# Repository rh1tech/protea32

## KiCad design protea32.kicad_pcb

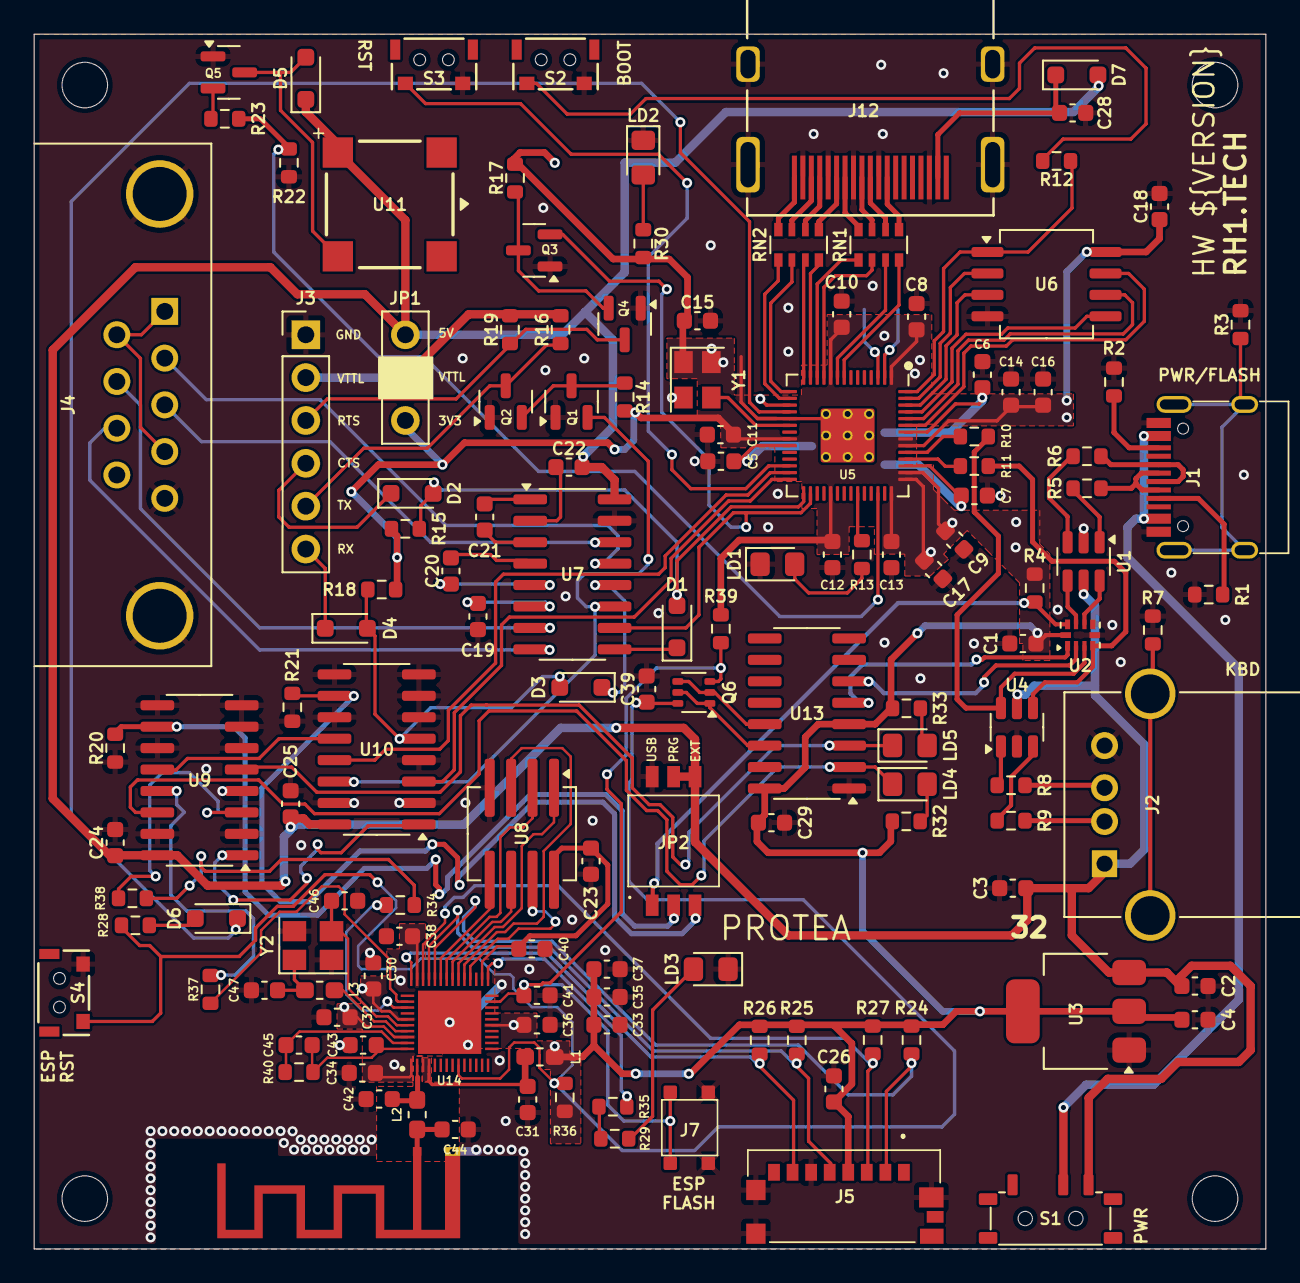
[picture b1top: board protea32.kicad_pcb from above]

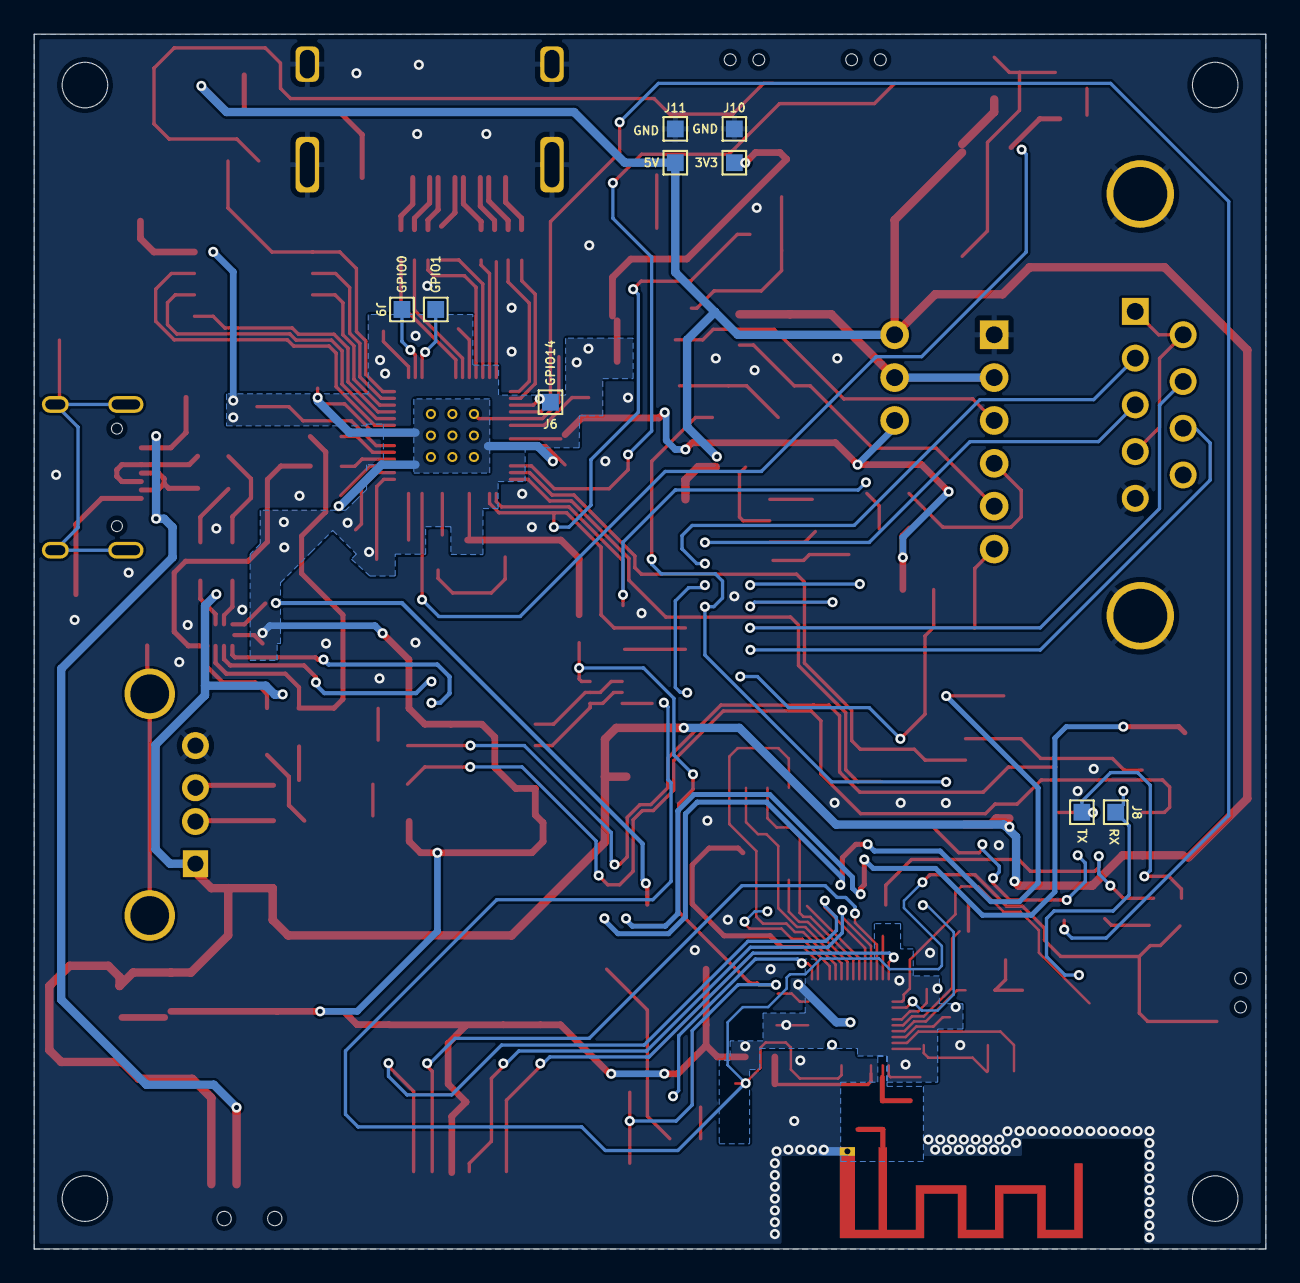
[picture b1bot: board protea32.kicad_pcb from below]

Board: 2 copper layers, 73.0 x 72.0 mm, 146 parts (5 on the bottom side), 128 nets.

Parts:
AE1: Antenna_Shield; Antenna (2.4GHz)
C1, C5, C6, C8, C10, C11, C12, C13, C14, C15, C16, C17, C18, C23, C24, C25, C26, C28, C29, C31, C33, C34, C36, C38: 100n; Capacitor (0603, S)
C2, C3, C4, C35: 10u; Capacitor (0603, S)
C7, C9, C19, C20, C21, C22, C30, C37, C40: 1u; Capacitor (0603, S)
C32: 100p; Capacitor (0603, S)
C39, C41: 1n; Capacitor (0603, S)
C42: 1.5pF; Capacitor (0603, S)
C43: 10n; Capacitor (0603, S)
C44: 2.4pF; Capacitor (0603, S)
C45: 3.3n; Capacitor (0603, S)
C46, C47: 12p; Capacitor (0603, S)
D1, D2, D3, D4, D5, D6: 1N4148; Diode (SOD-323)
D7: 1N5819WS; Diode (SOD-323)
H1, H2, H3, H4: MountingHole; Mounting Hole (2.7mm)
J1: USB4215-03-A; USB Type C
J2: 676430910; USB Type A (single)
J3: TTL; PinHeader_1x06_P2.54mm_Vertical
J4: D-SUB 9 Male; D-SUB (9 pin, male, top mount)
J5: 0475710001; MicroSD (SMD, short)
J6: Defaults; Test Point (1mm x 1)
J7: Flash; Button (SMD, 3x3mm, 1-1)
J8, J9, J10, J11: Test Points (1mm x 2)
J12: DC3RX19JA2; HDMI (female)
JP1: TTL PWR; PinHeader_1x03_P2.54mm_Vertical
JP2: Main Jumpers; DS05127203BKSMTTR
L1: 2nH; Inductor (0603 1.05x0.95)
L2: 2.7nH/0R; Inductor (0603 1.05x0.95)
L3: 24nH/0R; Inductor (0603 1.05x0.95)
LD1, LD3: Blue; LED (0805)
LD2: Green; LED (0805)
LD4, LD5: Orange; LED (0805)
Q1, Q2, Q3, Q4, Q5: 2N7000; SOT-23
Q6: UMH3N; SOT-363
R1, R2: 5.1K; Resistor (0603, S)
R3, R7: 1M; Resistor (0603, S)
R4, R20, R21, R22, R24, R25, R26, R27, R36, R39: 10K; Resistor (0603, S)
R5, R6, R8, R9: 22R; Resistor (0603, S)
R10, R11: 27R; Resistor (0603, S)
R12, R13, R14, R15, R17, R18, R30: 1K; Resistor (0603, S)
R16, R19, R29: 470R; Resistor (0603, S)
R23: 100R; Resistor (0603, S)
R28: 200R; Resistor (0603, S)
R32, R33: 1.5K; Resistor (0603, S)
R34: 499R; Resistor (0603, S)
R35: 0R; Resistor (0603, S)
R37, R38: 330R; Resistor (0603, S)
R40: 20K; Resistor (0603, S)
RN1, RN2: 270R; Resistor Array (4x0603)
S1: Power Switch; Switch (MSK12C02)
S2: Boot; TACT-SIDE-4623
S3: Reset; TACT-SIDE-4623
S4: ESP RST; TACT-SIDE-4623
U1, U4: USBLC6-2SC6; SOT-23-6
U2: TS3USB221RSER; UQFN-10
U3: NCP1117 3.3; SOT-223
U5: RP2040; QFN 56
U6: W25Q16JVSSIQ; SOIC-8
U7: MAX232CSE+; SOP-16
U8: W25Q32JVSIQ; SOIC-8 (Longer)
U9, U10: 74HC4052D; SOP-16
U11: CMT-7525-80-SMT-TR; CMT752580SMTTR
U13: CH340C; SOP-16
U14: ESP32-D0WD-V3; QFN35P500X500X90-49N-D
Y1: ASE-12MHz; Crystal (3225, active)
Y2: 40MHz; Crystal (3225)

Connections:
+3.3VP: C31.1, L1.2, U14.3 (VDD3P3_1), U14.4 (VDD3P3_2)
+3V3: C1.2, C4.1, C8.1, C9.1, C10.1, C11.1, C12.1, C13.1, C14.1, C15.1, C16.1, C17.1, C18.1, C26.2, C29.1, C30.1, C32.1, C33.1, C34.1, C35.1, C36.1, C37.1, C38.1, J5.P4 (VDD), J10.2, JP1.3, L1.1, R4.1, R14.2, R15.2, R17.2, R18.2, R24.2, R25.2, R26.2, R27.2, R30.2, R32.2, R33.1, R36.2, R39.2, U2.10 (VCC), U3.2 (VO), U5.1 (IOVDD), U5.10 (IOVDD), U5.22 (IOVDD), U5.33 (IOVDD), U5.42 (IOVDD), U5.43 (ADC_AVDD), U5.44 (VREG_IN), U5.48 (USB_VDD), U5.49 (IOVDD), U6.8 (VCC), U13.4 (3V), U13.16 (VCC), U14.1 (VDDA_1), U14.19 (VDD3P3_RTC), U14.37 (VDD3P3_CPU), U14.43 (VDDA_2), U14.46 (VDDA_3), Y1.1 (EN), Y1.4 (Vdd)
/ESP32/ANT: AE1.1 (A), C44.1, L2.1
/ESP32/CAP1: C43.1, C45.1, R40.2, U14.48 (CAP1)
/ESP32/CAP2: C45.2, R40.1, U14.47 (CAP2)
/ESP32/LNA_IN: C42.1, L2.2, U14.2 (LNA_IN)
/ESP32/XTAL_N: C46.1, U14.44 (XTAL_N), Y2.3
/ESP32/XTAL_P: L3.1, U14.45 (XTAL_P)
/ESP_CHIP_PU: C39.1, Q6.6 (C1), R28.1, R36.1, S4.1, U14.9 (CHIP_PU)
/ESP_DTR: Q6.2 (B1), Q6.4 (E2), U13.13 (DTR)
/ESP_GPIO0: C41.1, J7.2, Q6.3 (C2), R39.1, U14.23 (GPIO0)
/ESP_GPIO5: J5.P2 (CD/DAT3), R24.1, U14.34 (GPIO5)
/ESP_GPIO16: R29.1, R35.2
/ESP_GPIO18: J5.P5 (CLK), R25.1, U14.35 (GPIO18)
/ESP_GPIO19: J5.P7 (DAT0), R26.1, U14.38 (GPIO19)
/ESP_GPIO23: J5.P3 (CMD), R27.1, U14.36 (GPIO23)
/ESP_RTS: Q6.1 (E1), Q6.5 (B2), U13.14 (RTS)
/ESP_RXD: J8.1, R37.1, U9.13 (1Z)
/ESP_SCK/CLK: U8.6 (CLK), U14.31 (SD_CLK)
/ESP_SCS/CMD: U8.1 (~CS), U14.30 (SD_CMD)
/ESP_SDI/SD1: U8.5 (DI(IO0)), U14.33 (SD_DATA_1)
/ESP_SDO/SD0: U8.2 (DO(IO1)), U14.32 (SD_DATA_0)
/ESP_SHD/SD2: U8.7 (IO3), U14.28 (SD_DATA_2)
/ESP_SWP/SD3: U8.3 (IO2), U14.29 (SD_DATA_3)
/ESP_TXD: J8.2, R38.1, U9.3 (2Z)
/ESP_U0RXD: R37.2, U14.40 (U0RXD)
/ESP_U0TXD: R34.2, R38.2
/M1_SW: JP2.2, R20.2, U9.10 (S0)
/M2_SW: JP2.3, R21.2, U10.10 (S0)
/Multiplexers/MP_RX: U9.12 (1Y0), U10.12 (1Y0)
/Multiplexers/MP_TX: U9.1 (2Y0), U10.1 (2Y0)
/Power/UC_D+: U1.4 (I/O2), U2.8 (D+)
/Power/UC_D-: U1.6 (I/O1), U2.7 (D-)
/RP2040/GPIO25: R13.2, U5.37 (GPIO25)
/RP2040/QSPI_SCLK: U5.52 (QSPI_SCLK), U6.6 (CLK)
/RP2040/QSPI_SD0: U5.53 (QSPI_SD0), U6.5 (DI(IO0))
/RP2040/QSPI_SD1: U5.55 (QSPI_SD1), U6.2 (DO(IO1))
/RP2040/QSPI_SD2: U5.54 (QSPI_SD2), U6.3 (IO2)
/RP2040/QSPI_SD3: U5.51 (QSPI_SD3), U6.7 (IO3)
/RP2040/QSPI_SS: R12.1, U5.56 (QSPI_SS), U6.1 (~CS)
/RP2040/XIN: U5.20 (XIN), Y1.3 (OUT)
/RP_D+: R10.1, U2.3 (2D+), U4.6 (I/O1)
/RP_D-: R11.1, U2.4 (2D-), U4.4 (I/O2)
/RP_GPIO0: J9.1, U5.2 (GPIO0)
/RP_GPIO1: J9.2, U5.3 (GPIO1)
/RP_GPIO6: RN1.4 (R4.1), U5.8 (GPIO6)
/RP_GPIO7: RN1.3 (R3.1), U5.9 (GPIO7)
/RP_GPIO8: RN1.2 (R2.1), U5.11 (GPIO8)
/RP_GPIO9: RN1.1 (R1.1), U5.12 (GPIO9)
/RP_GPIO10: RN2.4 (R4.1), U5.13 (GPIO10)
/RP_GPIO11: RN2.3 (R3.1), U5.14 (GPIO11)
/RP_GPIO12: RN2.2 (R2.1), U5.15 (GPIO12)
/RP_GPIO13: RN2.1 (R1.1), U5.16 (GPIO13)
/RP_GPIO14: J6.1, U5.17 (GPIO14)
/RP_GPIO15: D6.1 (K), U5.18 (GPIO15)
/RP_GPIO16: U5.27 (GPIO16), U10.13 (1Z)
/RP_GPIO17: U5.28 (GPIO17), U10.3 (2Z)
/RP_GPIO18: D1.2 (A), D2.2 (A), R15.1, U5.29 (GPIO18)
/RP_GPIO19: Q3.2 (G), U5.30 (GPIO19), U7.10 (T2IN)
/RP_GPIO28: R22.2, R23.2, U5.40 (GPIO28_ADC2)
/RP_RUN: S3.1, U5.26 (RUN)
/RS232, TTL/C1+: C21.2, U7.1 (C1+)
/RS232, TTL/C1-: C21.1, U7.3 (C1-)
/RS232, TTL/C2+: C20.2, U7.4 (C2+)
/RS232, TTL/C2-: C20.1, U7.5 (C2-)
/RS232, TTL/CTS_IN: J4.7, U7.7 (T2OUT)
/RS232, TTL/CTS_MAX: D1.1 (K), U7.9 (R2OUT)
/RS232, TTL/CTS_TTL: D2.1 (K), J3.4
/RS232, TTL/RTS_IN: J4.8, U7.8 (R2IN)
/RS232, TTL/RTS_TTL: J3.3, Q4.3 (D), R19.1
/RS232, TTL/RX_IN: J4.3, U7.14 (T1OUT)
/RS232, TTL/RX_MAX: D3.1 (K), U7.12 (R1OUT)
/RS232, TTL/RX_TTL: D4.1 (K), J3.6
/RS232, TTL/TX_IN: J4.2, U7.13 (R1IN)
/RS232, TTL/TX_TTL: J3.5, Q2.3 (D), R16.1
/RS232, TTL/V+: C22.1, U7.2 (V+)
/RS232, TTL/V-: C19.1, U7.6 (V-)
/RS232, TTL/VTTL: J3.2, JP1.2, R16.2, R19.2
/RS232_RX: D3.2 (A), D4.2 (A), R18.1, U10.5 (2Y1)
/RS232_TX: Q1.2 (G), U7.11 (T1IN), U10.14 (1Y1)
/UMP_SW: JP2.1, R4.2, U2.9 (S)
/UT_D+: U2.1 (1D+), U13.5 (D+)
/UT_D-: U2.2 (1D-), U13.6 (D-)
/UT_RX: LD5.1 (K), U9.5 (2Y1), U13.3 (RxD)
/UT_TX: LD4.1 (K), U9.14 (1Y1), U13.2 (TxD)
/VDD_SDIO: C23.1, C40.1, U8.8 (VCC), U14.26 (VDD_SDIO)
GND: AE1.2 (Shield), C1.1, C2.2, C3.2, C4.2, C5.2, C6.2, C7.2, C8.2, C9.2, C10.2, C11.2, C12.2, C13.2, C14.2, C15.2, C16.2, C17.2, C18.2, C19.2, C23.2, C24.1, C25.1, C26.1, C28.2, C29.2, C30.2, C31.2, C32.2, C33.2, C34.2, C35.2, C36.2, C37.2, C38.2, C39.2, C40.2, C41.2, C42.2, C43.2, C44.2, C46.2, C47.2, J1.1 (GND), J1.12 (GND), J2.4 (GND), J3.1, J4.5, J5.G1 (GND_1), J5.G2 (GND_2), J5.G3 (GND_3), J5.P6 (VSS), J7.1, J10.1, J11.1, J12.2 (G_D2), J12.5 (G_D1), J12.8 (G_D0), J12.11 (G_CLK), J12.17 (G_DDC/CEC), J12.20 (SHIELD1), J12.21 (SHIELD2), J12.22 (SHIELD3), J12.23 (SHIELD4), JP2.6, LD1.1 (K), LD2.1 (K), LD3.1 (K), Q1.1 (S), Q2.1 (S), Q3.1 (S), Q4.1 (S), Q5.1 (S), R1.1, R2.1, R3.2, R7.2, R20.1, R21.1, R22.1, S2.2, S3.2, S4.2, U1.2 (GND), U2.5 (GND), U2.6 (~OE), U3.1 (GND), U4.2 (GND), U5.19 (TESTEN), U5.57 (GND), U6.4 (GND), U7.15 (GND), U8.4 (GND), U9.2 (2Y2), U9.4 (2Y3), U9.6 (~E), U9.7 (VEE), U9.8 (GND), U9.9 (S1), U9.11 (1Y3), U9.15 (1Y2), U10.2 (2Y2), U10.4 (2Y3), U10.6 (~E), U10.7 (VEE), U10.8 (GND), U10.9 (S1), U10.11 (1Y3), U10.15 (1Y2), U13.1 (GND), U14.49 (GND), Y1.2 (GND), Y2.2, Y2.4
unnamed: C47.1, L3.2, Y2.1
unnamed: D5.2 (A), Q5.3 (D), U11.2 (-)
unnamed: D6.2 (A), R28.2
unnamed: C28.1, D7.1 (K), J12.18 (+5V)
unnamed: J1.4 (CC1), R1.2
unnamed: J1.10 (CC2), R2.2
unnamed: J1.5 (DN2), J1.7 (DN1), R5.2
unnamed: J1.6 (DP1), J1.8 (DP2), R6.2
unnamed: J1.13 (SHIELD), R3.1
unnamed: J2.3 (D+), R8.2
unnamed: J2.2 (D-), R9.2
unnamed: J2.5 (Shield), R7.1
unnamed: J4.1, J4.4, J4.6
unnamed: J12.12 (CLKN), RN1.5 (R4.2)
unnamed: J12.10 (CLKP), RN1.6 (R3.2)
unnamed: J12.9 (D0N), RN1.7 (R2.2)
unnamed: J12.7 (D0P), RN1.8 (R1.2)
unnamed: J12.6 (D1N), RN2.5 (R4.2)
unnamed: J12.4 (D1P), RN2.6 (R3.2)
unnamed: J12.3 (D2N), RN2.7 (R2.2)
unnamed: J12.1 (D2P), RN2.8 (R1.2)
unnamed: LD1.2 (A), R13.1
unnamed: LD2.2 (A), R30.1
unnamed: LD3.2 (A), R29.2
unnamed: LD4.2 (A), R32.1
unnamed: LD5.2 (A), R33.2
unnamed: Q1.3 (D), Q2.2 (G), R14.1
unnamed: Q3.3 (D), Q4.2 (G), R17.1
unnamed: Q5.2 (G), R23.1
unnamed: R5.1, U1.1 (I/O1)
unnamed: R6.1, U1.3 (I/O2)
unnamed: R8.1, U4.1 (I/O1)
unnamed: R9.1, U4.3 (I/O2)
unnamed: R12.2, S2.1
unnamed: J1.2 (VBUS), J1.11 (VBUS), S1.2 (B)
unnamed: R11.2, U5.46 (USB_DM)
unnamed: R10.2, U5.47 (USB_DP)
unnamed: C5.1, C6.1, C7.1, U5.23 (DVDD), U5.45 (VREG_VOUT), U5.50 (DVDD)
unnamed: R35.1, U14.25 (GPIO16)
unnamed: R34.1, U14.41 (U0TXD)
VBUS: C2.1, C3.1, C22.2, C24.2, C25.2, D5.1 (K), D7.2 (A), J2.1 (VBUS), J11.2, JP1.1, JP2.4, JP2.5, S1.3 (A), U1.5 (VBUS), U3.3 (VI), U4.5 (VBUS), U7.16 (VCC), U9.16 (VCC), U10.16 (VCC), U11.1 (+)

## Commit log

2025-10-18 Routing WIP
2025-10-19 Cleanup WIP
2025-10-19 HW 1.00
2025-11-08 HW 1.01
2025-11-10 HW 1.01 Release
2025-11-10 HW 1.01 Release (fixed)
